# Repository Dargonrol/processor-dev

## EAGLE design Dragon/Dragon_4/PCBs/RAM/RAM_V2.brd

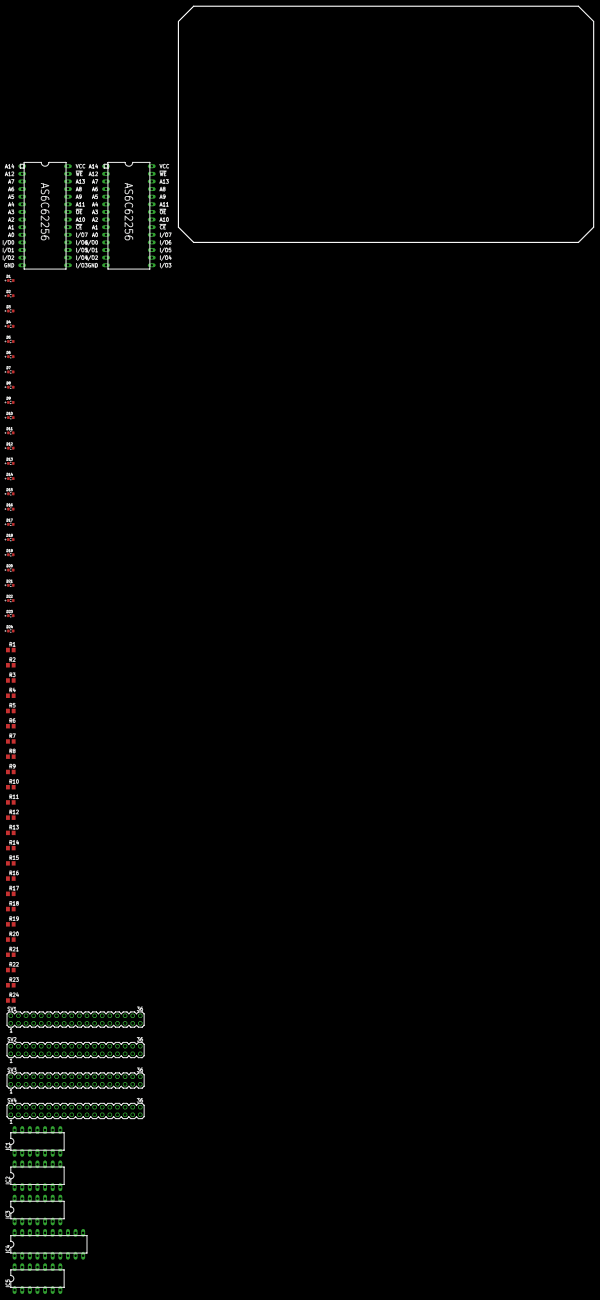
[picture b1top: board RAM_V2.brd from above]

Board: 2 copper layers, 138.4 x 78.7 mm, 59 parts (0 on the bottom side), 64 nets, no tracks yet.

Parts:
D1, D2, D3, D4, D5, D6, D7, D8, D9, D10, D11, D12, D13, D14, D15, D16, D17, D18, D19, D20, D21, D22, D23, D24: LTST-C193KRKT-5A; LEDC1608X45N
IC1: 74HCT04N; DIL14
IC2, IC5: 74HCT32N; DIL14
IC3: 74HCT08N; DIL14
IC4: 74HCT245N; DIL20
R1, R2, R3, R4, R5, R6, R7, R8, R9, R10, R11, R12, R13, R14, R15, R16, R17, R18, R19, R20, R21, R22, R23, R24: R0805
SV1, SV2, SV3, SV4: MA18-2
U$1, U$2: AS6C62256

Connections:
!CLK: IC2.1, IC2.13
ADDRESS_BUS_0: D1.A, U$1.A0, U$2.A0
ADDRESS_BUS_1: D2.A, U$1.A1, U$2.A1
ADDRESS_BUS_2: D3.A, U$1.A2, U$2.A2
ADDRESS_BUS_3: D4.A, U$1.A3, U$2.A3
ADDRESS_BUS_4: D5.A, U$1.A4, U$2.A4
ADDRESS_BUS_5: D6.A, U$1.A5, U$2.A5
ADDRESS_BUS_6: D7.A, U$1.A6, U$2.A6
ADDRESS_BUS_7: D8.A, U$1.A7, U$2.A7
ADDRESS_BUS_8: D9.A, U$1.A8, U$2.A8
ADDRESS_BUS_9: D10.A, U$1.A9, U$2.A9
ADDRESS_BUS_10: D11.A, U$1.A10, U$2.A10
ADDRESS_BUS_11: D12.A, U$1.A11, U$2.A11
ADDRESS_BUS_12: D13.A, U$1.A12, U$2.A12
ADDRESS_BUS_13: D14.A, U$1.A13, U$2.A13
ADDRESS_BUS_14: D15.A, U$1.A14, U$2.A14
ADDRESS_BUS_15: D16.A, IC1.1, IC1.3, IC1.9, IC2.4, IC5.2, U$1.!CE
AYETG: IC1.5, IC1.11, IC2.5, IC2.12, IC3.3, IC3.4
DATA_BUS_0: D17.A, IC4.18, U$1.I/O0, U$2.I/O0
DATA_BUS_1: D18.A, IC4.17, U$1.I/O1, U$2.I/O1
DATA_BUS_2: D19.A, IC4.16, U$1.I/O2, U$2.I/O2
DATA_BUS_3: D20.A, IC4.15, U$1.I/O3, U$2.I/O3
DATA_BUS_4: D21.A, IC4.14, U$1.I/O4, U$2.I/O4
DATA_BUS_5: D22.A, IC4.13, U$1.I/O5, U$2.I/O5
DATA_BUS_6: D23.A, IC4.12, U$1.I/O6, U$2.I/O6
DATA_BUS_7: D24.A, IC4.11, U$1.I/O7, U$2.I/O7
GND: IC1.7, IC2.7, IC3.7, IC4.10, IC5.7, R1.1, R2.1, R3.1, R4.1, R5.1, R6.1, R7.1, R8.1, R9.1, R10.1, R11.1, R12.1, R13.1, R14.1, R15.1, R16.1, R17.1, R18.1, R19.1, R20.1, R21.1, R22.1, R23.1, R24.1, U$1.GND, U$2.GND
unnamed: D1.C, R1.2
unnamed: D2.C, R2.2
unnamed: D3.C, R3.2
unnamed: D4.C, R4.2
unnamed: D5.C, R5.2
unnamed: D6.C, R6.2
unnamed: D7.C, R7.2
unnamed: D8.C, R8.2
unnamed: D9.C, R9.2
unnamed: D10.C, R10.2
unnamed: D11.C, R11.2
unnamed: D12.C, R12.2
unnamed: D13.C, R13.2
unnamed: D14.C, R14.2
unnamed: D15.C, R15.2
unnamed: D16.C, R16.2
unnamed: D17.C, R17.2
unnamed: D18.C, R18.2
unnamed: D20.C, R20.2
unnamed: D21.C, R21.2
unnamed: D22.C, R22.2
unnamed: D23.C, R23.2
unnamed: D24.C, R24.2
unnamed: IC2.3, U$1.!WE
unnamed: IC5.3, U$1.!OE
unnamed: IC2.2, IC2.6
unnamed: IC2.8, U$2.!WE
unnamed: IC5.6, U$2.!OE
unnamed: IC1.2, U$2.!CE
unnamed: D19.C, R19.2
unnamed: IC2.10, IC2.11
unnamed: IC1.4, IC2.9
unnamed: IC1.6, IC5.1, IC5.4
unnamed: IC1.8, IC5.5
unnamed: IC1.10, IC4.1
unnamed: IC3.6, IC4.19
VCC: IC1.14, IC2.14, IC3.14, IC4.20, IC5.14, U$1.VCC, U$2.VCC
